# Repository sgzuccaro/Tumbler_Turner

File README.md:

# Tumbler_Turner
 This Repo includes all the electrical/mechanical/software required for the tumbler turner.
 
 # PCB Design
 The PCB will use an arduino NANO, a a4988 stepper driver

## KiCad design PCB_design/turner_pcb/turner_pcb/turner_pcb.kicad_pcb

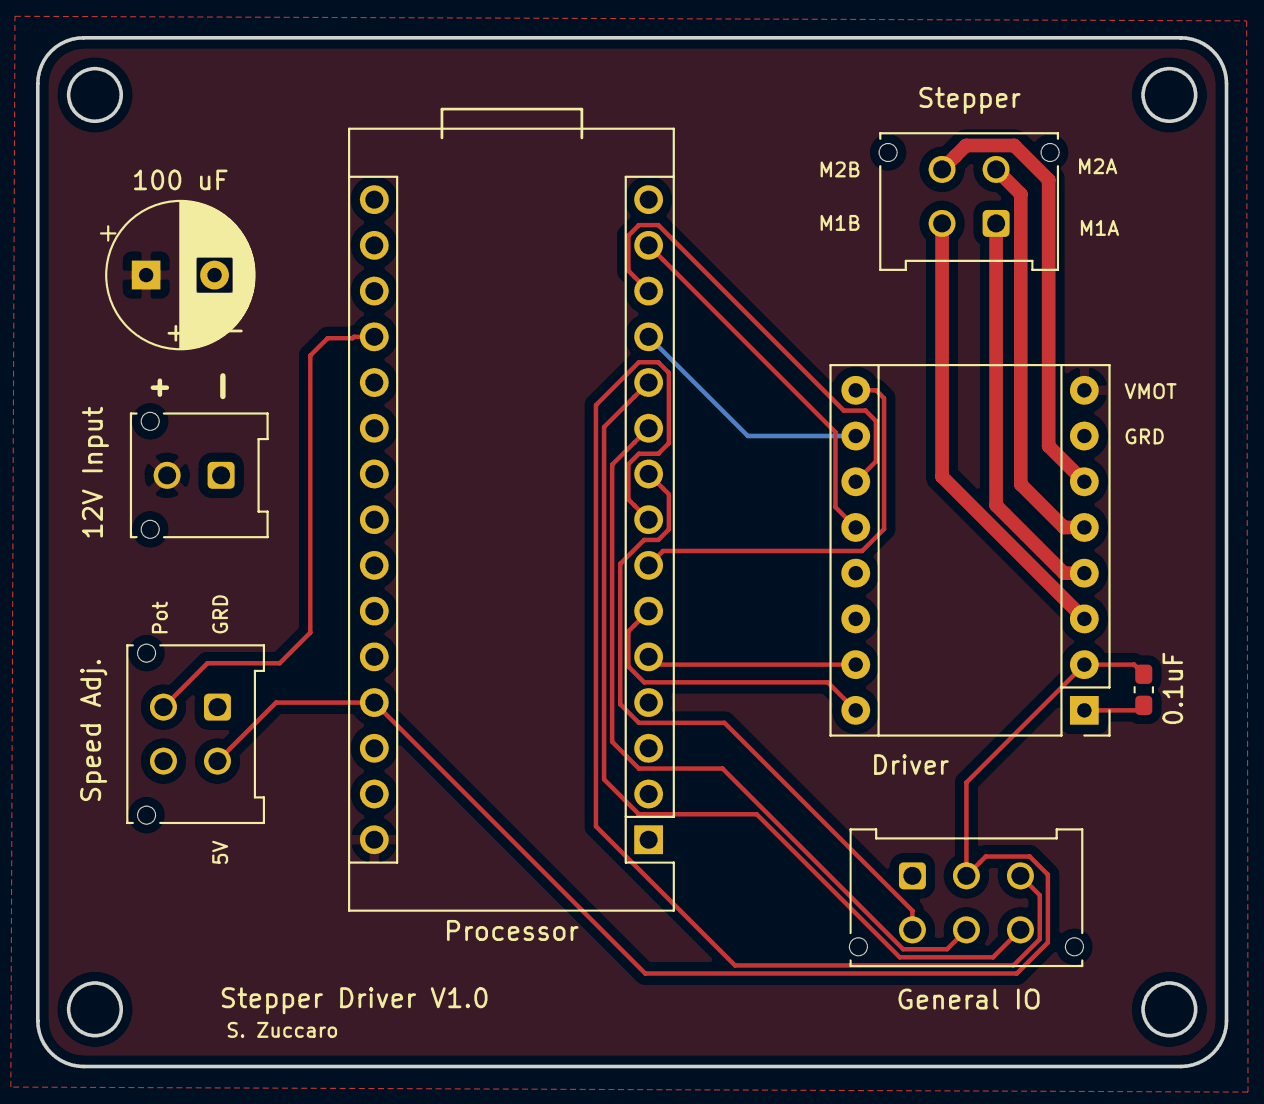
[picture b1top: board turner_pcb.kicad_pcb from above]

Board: 2 copper layers, 66.0 x 57.1 mm, 8 parts (0 on the bottom side), 18 nets.

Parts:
0.1uF: C; C_0603_1608Metric_Pad1.08x0.95mm_HandSolder
12V Input: Conn_01x02; Molex_Micro-Fit_3.0_43045-0212_2x01_P3.00mm_Vertical
100 uF: C_Polarized; CP_Radial_D8.0mm_P3.80mm
Driver: Pololu_Breakout_A4988; Pololu_Breakout-16_15.2x20.3mm
General IO: Conn_02x03_Odd_Even; Molex_Micro-Fit_3.0_43045-0612_2x03_P3.00mm_Vertical
Processor: Arduino_Nano_v3.x; Arduino_Nano
Speed Adj.: Conn_02x02_Odd_Even; Molex_Micro-Fit_3.0_43045-0412_2x02_P3.00mm_Vertical
Stepper: Conn_02x02_Odd_Even; Molex_Micro-Fit_3.0_43045-0412_2x02_P3.00mm_Vertical

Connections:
+5V: 0.1uF.1, Driver.2, General IO.2, Processor.27, Speed Adj..2
+12V: 12V Input.2, 100 uF.1, Driver.8, Processor.30
DIO1: General IO.3, Processor.8
DIO2: General IO.4, Processor.9
DIO3: General IO.5, Processor.10
DIO4: General IO.6, Processor.11
Direction: Driver.16, Processor.6
Enable: Driver.9, Processor.7
GND: 0.1uF.2, 12V Input.1, 100 uF.2, Driver.1, Driver.7, Driver.13, Driver.14, General IO.1, Processor.4, Speed Adj..1
M1A: Driver.4, Stepper.1
M1B: Driver.3, Stepper.2
M2A: Driver.5, Stepper.3
M2B: Driver.6, Stepper.4
MS1: Driver.10, Processor.12
MS2: Driver.11, Processor.13
MS3: Driver.12, Processor.14
Pot: Processor.19, Speed Adj..3
Step: Driver.15, Processor.5

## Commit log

2021-01-05 started with arduni nano templete
    This pcb design is based on the provided kicad templete for arduino nano.
2021-01-08 draft of firmware, learning proper step spacing
2021-01-13 added nano sch
2021-01-28 First version of working firmware.
2021-01-31 first attempt at including tmc2208
2021-04-07 first complete version on pcb
2021-04-08 worked on pcb design
2021-04-09 pcb design V1.0 sent to JLCPCB
2021-04-21 first working version v1
